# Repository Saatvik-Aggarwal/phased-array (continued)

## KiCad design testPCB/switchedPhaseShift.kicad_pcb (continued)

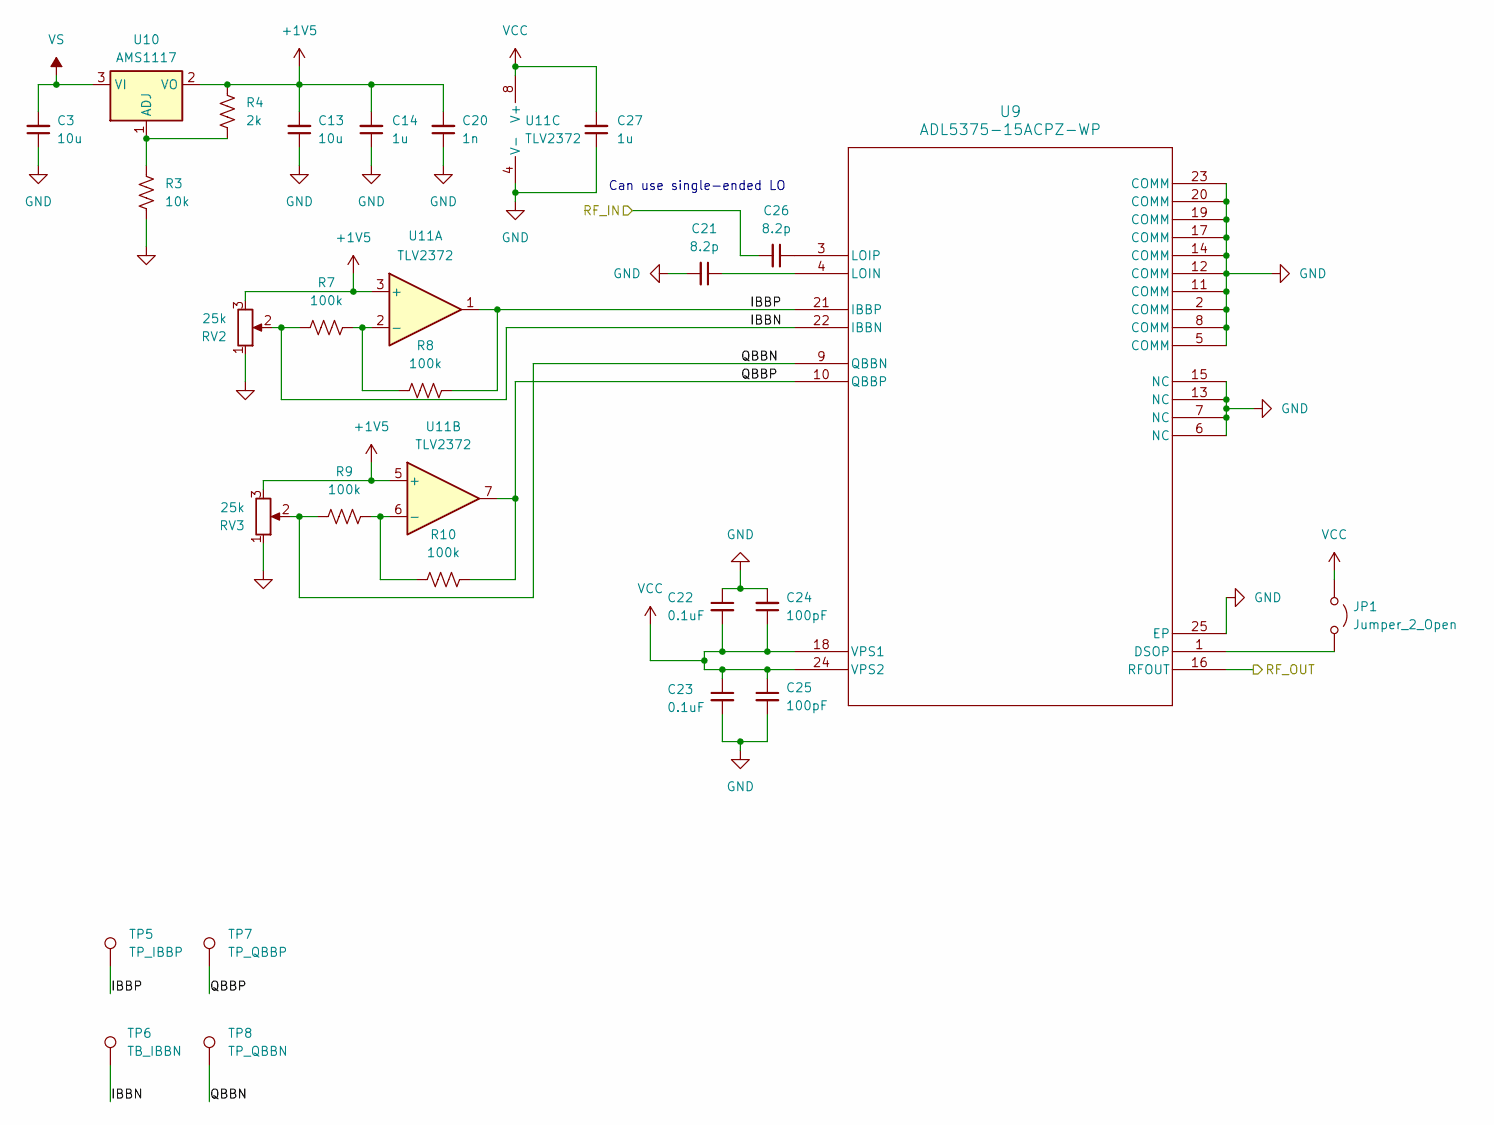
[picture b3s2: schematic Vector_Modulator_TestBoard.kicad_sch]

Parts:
C3, C13: 10u; C_0603_1608Metric_Pad1.08x0.95mm_HandSolder
C14, C27: 1u; C_0603_1608Metric_Pad1.08x0.95mm_HandSolder
C20: 1n; C_0603_1608Metric_Pad1.08x0.95mm_HandSolder
C21, C26: 8.2p; C_0201_0603Metric_Pad0.64x0.40mm_HandSolder
C22, C23: 0.1uF; C_0603_1608Metric_Pad1.08x0.95mm_HandSolder
C24, C25: 100pF; C_0603_1608Metric_Pad1.08x0.95mm_HandSolder
JP1: Jumper_2_Open; SolderJumper-2_P1.3mm_Open_RoundedPad1.0x1.5mm
R3: 10k; R_0603_1608Metric_Pad0.98x0.95mm_HandSolder
R4: 2k; R_0603_1608Metric_Pad0.98x0.95mm_HandSolder
R7, R8, R9, R10: 100k; R_0603_1608Metric_Pad0.98x0.95mm_HandSolder
RV2, RV3: 25k; Potentiometer_Bourns_3386X_Horizontal
TP5: TP_IBBP; TestPoint_Pad_1.5x1.5mm
TP6: TB_IBBN; TestPoint_Pad_1.5x1.5mm
TP7: TP_QBBP; TestPoint_Pad_1.5x1.5mm
TP8: TP_QBBN; TestPoint_Pad_1.5x1.5mm
U9: ADL5375-15ACPZ-WP; LFCSP-24-1EP_4x4mm_P0.5mm_EP2.3x2.3mm_ThermalVias
U10: AMS1117; SOT-223-3_TabPin2
U11: TLV2372; SOIC-8_3.9x4.9mm_P1.27mm

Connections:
+1V5: C13.2, C14.2, C20.2, R4.1, RV2.3, RV3.3, U10.2 (VO), U11.3 (+), U11.5 (+)
/VectorModulator/IBBN: R7.1, RV2.2, TP6.1, U9.22 (IBBN); also elsewhere on the board
/VectorModulator/QBBN: R9.1, RV3.2, TP8.1, U9.9 (QBBN); also elsewhere on the board
/VectorModulator/QBBP: R10.2, TP7.1, U9.10 (QBBP), U11.7; also elsewhere on the board
/VectorModulator/RF_IN: C26.2; also elsewhere on the board
/VectorModulator/RF_OUT: U9.16 (RFOUT); also elsewhere on the board
unnamed: JP1.2 (B), U9.1 (DSOP)
unnamed: C21.1, U9.4 (LOIN)
unnamed: C26.1, U9.3 (LOIP)
unnamed: R3.1, R4.2, U10.1 (ADJ)
unnamed: R7.2, R8.1, U11.2 (-)
unnamed: R9.2, R10.1, U11.6 (-)
VCC: C22.2, C23.1, C24.1, C25.1, C27.2, JP1.1 (A), U9.18 (VPS1), U9.24 (VPS2), U11.8 (V+); also elsewhere on the board
VS: C3.2, U10.3 (VI); also elsewhere on the board

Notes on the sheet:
Can use single-ended LO

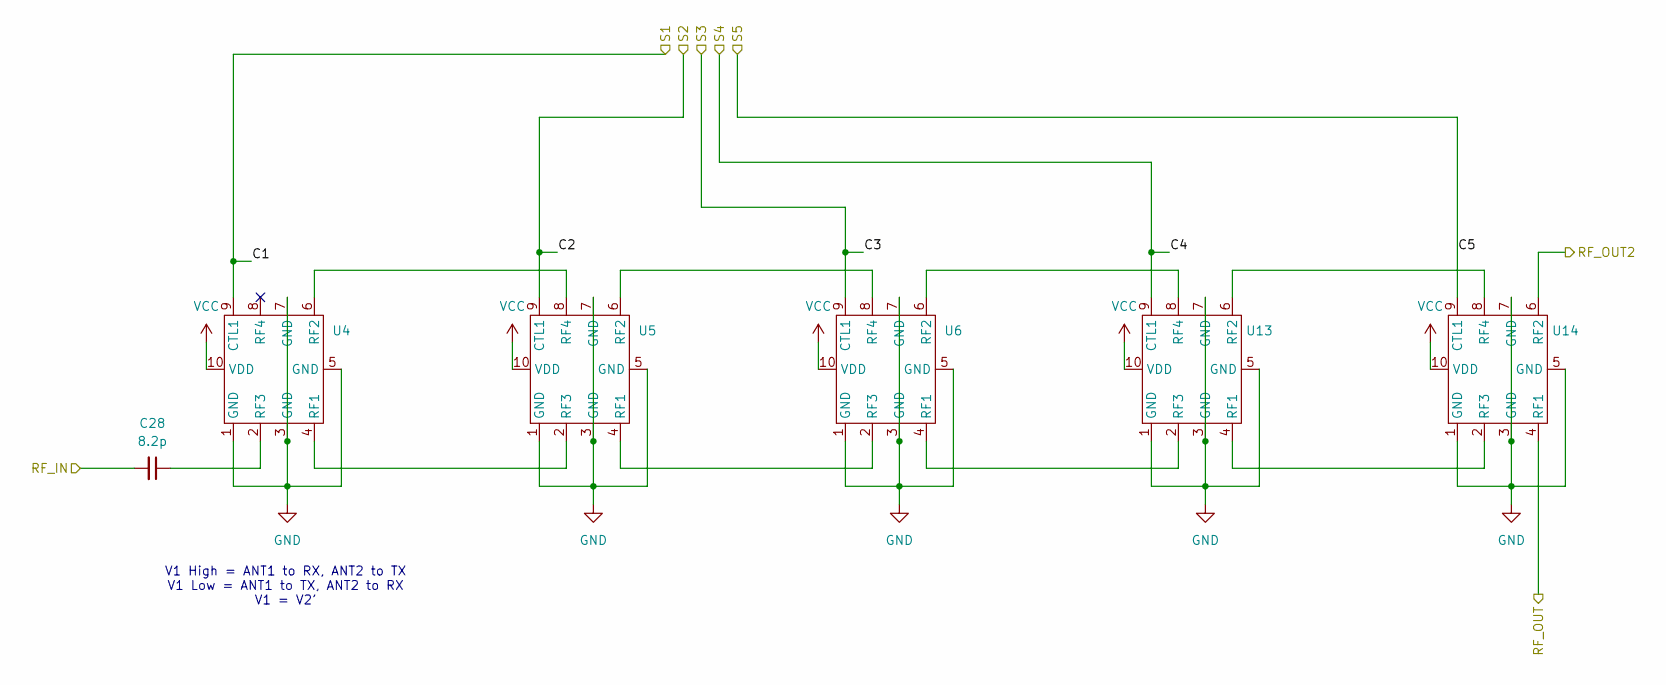
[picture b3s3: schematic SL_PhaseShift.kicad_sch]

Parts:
C28: 8.2p; C_0201_0603Metric_Pad0.64x0.40mm_HandSolder
U4, U5, U6, U13, U14: SKY13699-21

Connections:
/Amplifier_SBB5089Z/RF_IN: U14.4 (RF1); also elsewhere on the board
/SL_PhaseShift1/C1: U4.9 (CTL1); also elsewhere on the board
/SL_PhaseShift1/C2: U5.9 (CTL1); also elsewhere on the board
/SL_PhaseShift1/C3: U6.9 (CTL1); also elsewhere on the board
/SL_PhaseShift1/C4: U13.9 (CTL1); also elsewhere on the board
/SL_PhaseShift1/C5: U14.9 (CTL1); also elsewhere on the board
/SL_PhaseShift1/RF_IN: C28.2; also elsewhere on the board
/SL_PhaseShift1/RF_OUT2: U14.6 (RF2); also elsewhere on the board
unnamed: U4.4 (RF1), U5.2 (RF3)
unnamed: U4.6 (RF2), U5.8 (RF4)
unnamed: C28.1, U4.2 (RF3)
unnamed: U5.4 (RF1), U6.2 (RF3)
unnamed: U5.6 (RF2), U6.8 (RF4)
unnamed: U13.4 (RF1), U14.2 (RF3)
unnamed: U13.6 (RF2), U14.8 (RF4)
unnamed: U6.4 (RF1), U13.2 (RF3)
unnamed: U6.6 (RF2), U13.8 (RF4)
VCC: U4.10 (VDD), U5.10 (VDD), U6.10 (VDD), U13.10 (VDD), U14.10 (VDD); also elsewhere on the board

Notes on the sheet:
V1 High = ANT1 to RX, ANT2 to TX V1 Low = ANT1 to TX, ANT2 to RX V1 = V2'

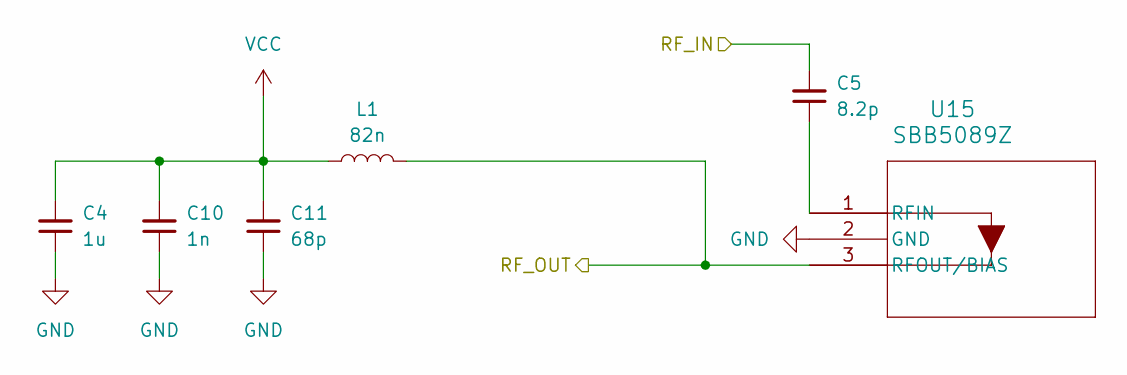
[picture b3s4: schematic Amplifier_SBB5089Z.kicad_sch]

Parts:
C4: 1u; C_0603_1608Metric_Pad1.08x0.95mm_HandSolder
C5: 8.2p; C_0201_0603Metric_Pad0.64x0.40mm_HandSolder
C10: 1n; C_0603_1608Metric_Pad1.08x0.95mm_HandSolder
C11: 68p; C_0201_0603Metric_Pad0.64x0.40mm_HandSolder
L1: 82n; L_0402_1005Metric_Pad0.77x0.64mm_HandSolder
U15: SBB5089Z; SOT_SBB5089Z_QOR

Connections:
/Amplifier_SBB5089Z/RF_IN: C5.2; also elsewhere on the board
/Amplifier_SBB5089Z/RF_OUT: L1.2, U15.3 (RFOUT/BIAS); also elsewhere on the board
unnamed: C5.1, U15.1 (RFIN)
VCC: C4.2, C10.2, C11.2, L1.1; also elsewhere on the board

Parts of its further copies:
C1: 1u; C_0603_1608Metric_Pad1.08x0.95mm_HandSolder
C7: 1n; C_0603_1608Metric_Pad1.08x0.95mm_HandSolder
C8: 68p; C_0201_0603Metric_Pad0.64x0.40mm_HandSolder
C9: 8.2p; C_0201_0603Metric_Pad0.64x0.40mm_HandSolder
L2: 82n; L_0402_1005Metric_Pad0.77x0.64mm_HandSolder
U3: SBB5089Z; SOT_SBB5089Z_QOR

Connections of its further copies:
/Amplifier_SBB5089Z1/RF_IN: C9.2; also elsewhere on the board
/Amplifier_SBB5089Z1/RF_OUT: L2.2, U3.3 (RFOUT/BIAS); also elsewhere on the board
unnamed: C9.1, U3.1 (RFIN)
VCC: C1.2, C7.2, C8.2, L2.1; also elsewhere on the board

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
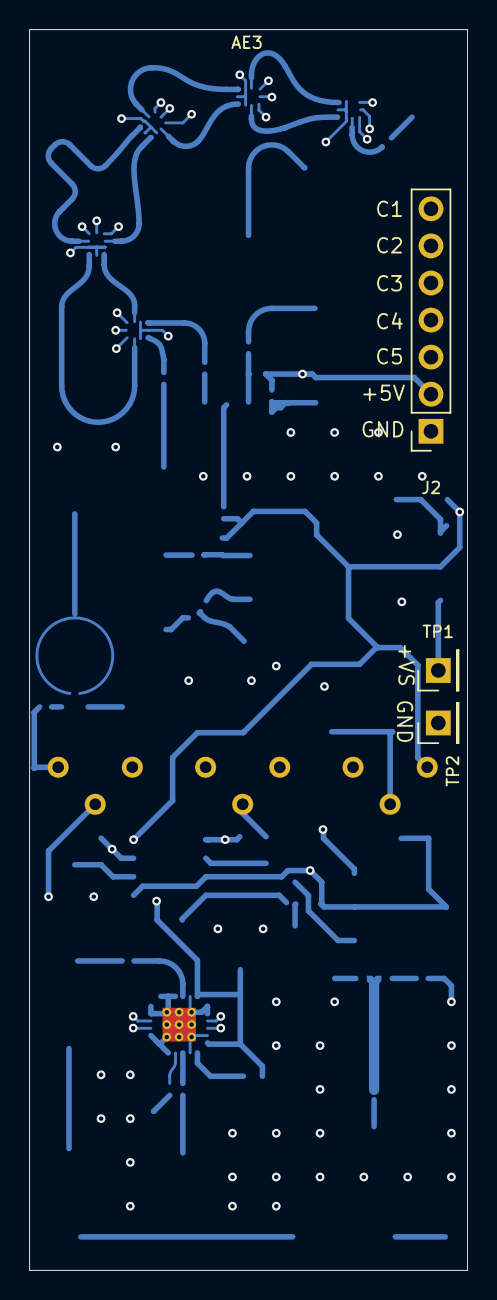
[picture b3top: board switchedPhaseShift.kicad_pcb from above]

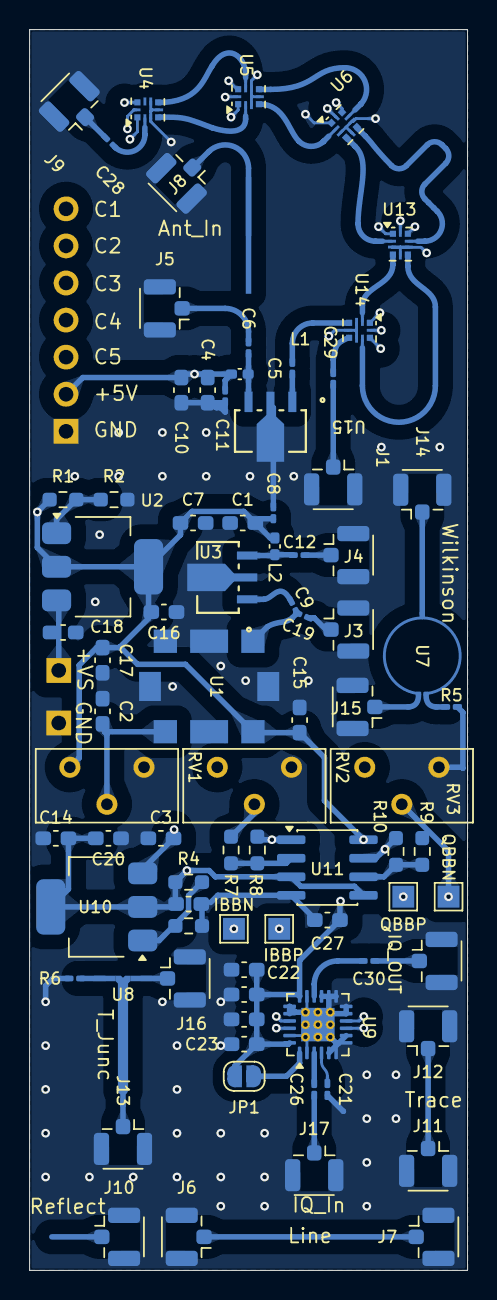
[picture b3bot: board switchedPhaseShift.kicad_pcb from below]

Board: 4 copper layers, 30.0 x 85.0 mm, 85 parts (81 on the bottom side), 54 nets.

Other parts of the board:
IBBN: TB_IBBN; TestPoint_Pad_1.5x1.5mm
IBBP: TP_IBBP; TestPoint_Pad_1.5x1.5mm
IQ_OUT: Conn_Coaxial; U.FL_Hirose_U.FL-R-SMT-1_Vertical
QBBN: TP_QBBN; TestPoint_Pad_1.5x1.5mm
QBBP: TP_QBBP; TestPoint_Pad_1.5x1.5mm

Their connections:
/VectorModulator/IBBN: IBBN.1; also elsewhere on the board
/VectorModulator/QBBN: QBBN.1; also elsewhere on the board
/VectorModulator/QBBP: QBBP.1; also elsewhere on the board
unnamed 29: IQ_OUT.1 (In); also elsewhere on the board

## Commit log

2025-11-04 Created using Colab
2025-11-18 This code takes a target direction (elevation, azimuth), converts it into direction-cosines (u, v), computes the required phase shift for each element of the 4×4 array, and outputs quantized N-bit ph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
2026-02-11 create gitignore
2026-02-11 gitignore includes logs
2026-02-11 testPCB
2026-02-12 minor design fixes for test pcb
    - gnd plane should not be on f.cu
    - remove solder mask on f.cu over antenna
    - add DC block capacitors on board outputs to VNA (to J1 and J18)
2026-02-13 generate gerbers
2026-03-02 Rename Beamforming_Algorithm.ipynb to Beamforming_Simulation.ipynb
2026-03-19 4 element phase shifter designed
2026-03-19 add new 4 element PCB
2026-03-19 deep's reciever project added
2026-03-20 gerbers generated for 4 element
2026-03-24 updated resistor values
2026-03-24 rx schematic drawn, need to update values
2026-03-25 pcb for rx made
2026-03-25 updated impedance matching
2026-03-25 checked drc and fixed gnd plane
2026-04-08 saatvik mad
